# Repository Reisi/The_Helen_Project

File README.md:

# Helen

The Helen Project is a firmware platform for bicycle lights.
It features

- up to 8 modes, each individually configurable
- the modes can be split into groups
- support for remote control connected over BLE
- mode and group configurations with The Helen App
- light-to-light connections with mode synchronization

Currently there are two devices:

- [Helen](HELEN.md), an alternative electronic circuit for the Yinding or KD2 headlight cycling lamps
- [Drake](https://github.com/Reisi/Drake), a multi-purpose PCB, which can be used to build a rear light or a dropper post actuator

## License

This project is licensed under the BSD-2-clause License - see the [license.txt](license.txt) file for details

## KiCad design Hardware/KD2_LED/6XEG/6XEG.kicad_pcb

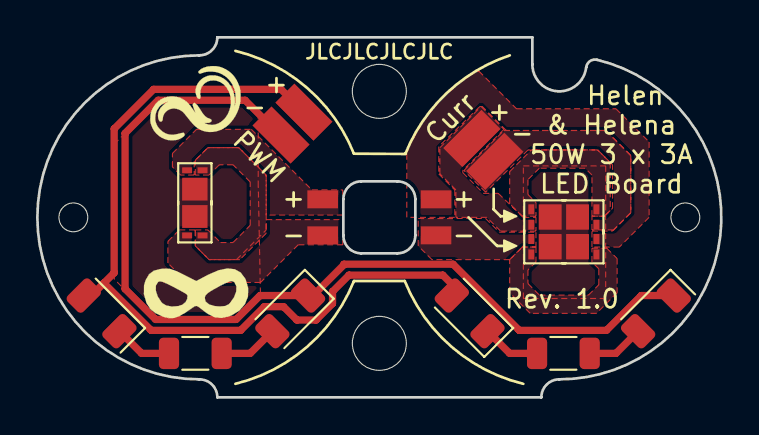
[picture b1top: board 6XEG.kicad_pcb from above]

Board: 2 copper layers, 38.0 x 20.0 mm, 17 parts (0 on the bottom side), 17 nets.

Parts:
D1, D2, D3, D4, D5, D6: LED_PAD; LED_Cree-XE-G
D7, D8, D9, D10: LED; LED_1206_3216Metric
J1: Conn_02x02_Odd_Even; PinHeader_2x02_P2.00mm_Vertical_SMD
J2, J3, J4, J5: Conn_01x01; 1,5x3mm_SMD
R1, R2: R; R_1206_3216Metric

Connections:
unnamed: D1.1, D2.2
unnamed: D1.2, J1.1
unnamed: D1.3, D2.3
unnamed: D2.1, J1.3
unnamed: D3.1, D4.2
unnamed: D3.2, J2.1
unnamed: D3.3, D4.3, D5.3, D6.3
unnamed: D4.1, J3.1
unnamed: D5.1, D6.2
unnamed: D5.2, J1.2
unnamed: D6.1, J1.4
unnamed: D7.1, R1.1
unnamed: D7.2, D8.2, J4.1
unnamed: D8.1, R2.1
unnamed: D9.2, R1.2
unnamed: D9.1, D10.1, J5.1
unnamed: D10.2, R2.2

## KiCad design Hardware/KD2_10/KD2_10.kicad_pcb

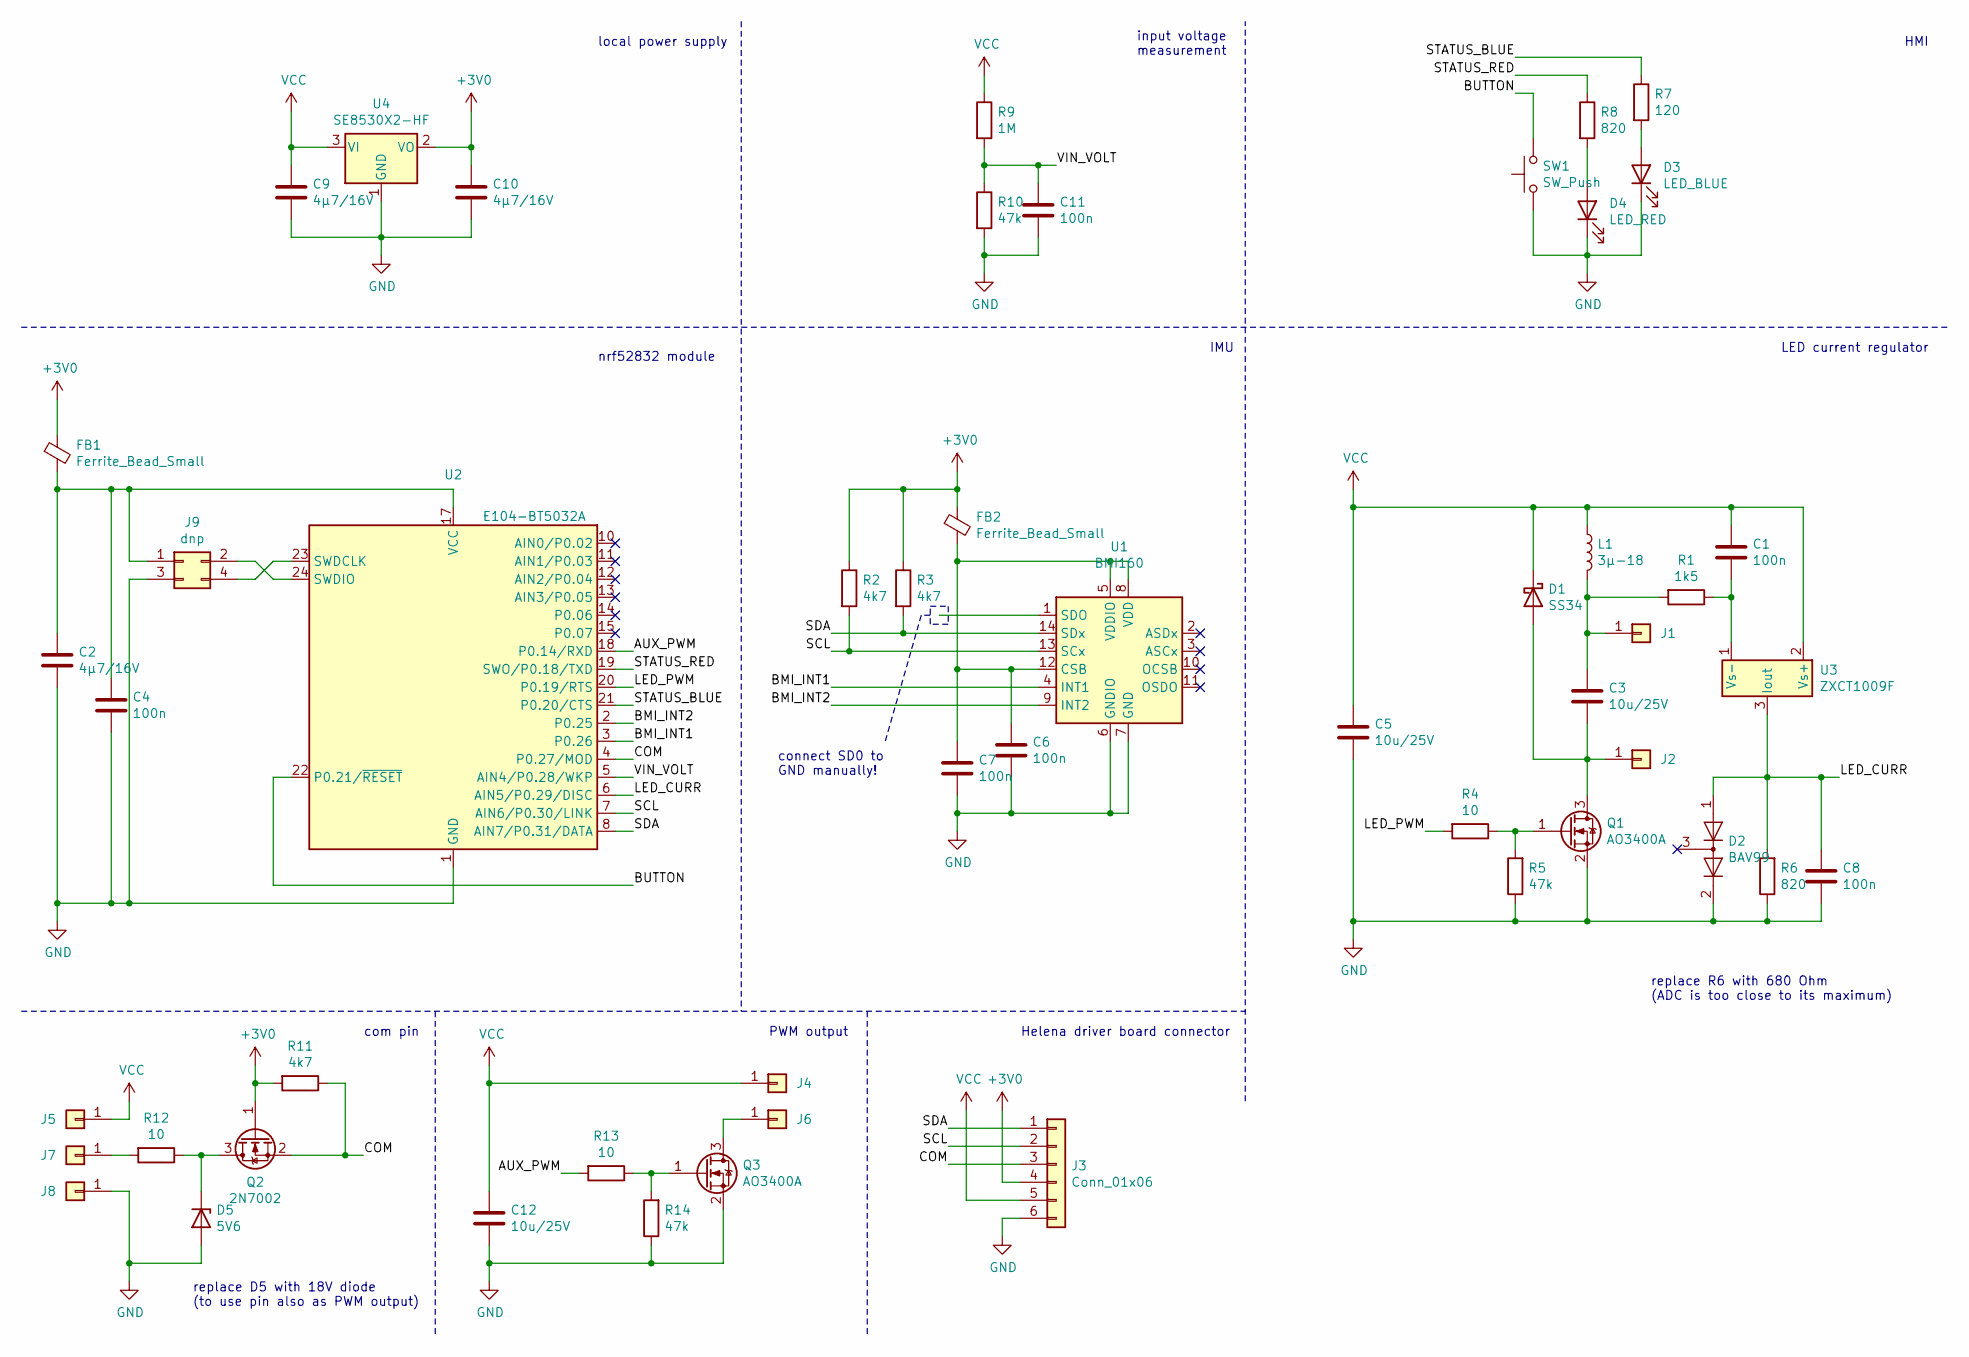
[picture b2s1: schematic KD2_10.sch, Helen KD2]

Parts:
C1, C4, C6, C7, C8, C11: 100n; C_0603_1608Metric; JLC 0603
C2, C9, C10: 4µ7/16V; C_0603_1608Metric; JLC 0603
C3, C5, C12: 10u/25V; C_0805_2012Metric; JLC 0805
D1: SS34; D_SMA; JLC SMA,DO-214AC
D2: BAV99; SOT-23; JLC SOT-23-3
D3: LED_BLUE; LED_0603_1608Metric; JLC LED_0603
D4: LED_RED; LED_0603_1608Metric; JLC LED_0603
D5: 5V6; D_SOT-23_ANK; JLC SOT-23-3
FB1, FB2: Ferrite_Bead_Small; L_0603_1608Metric; JLC 0603
J1, J2, J4, J5, J6, J7, J8: Conn_01x01; 1,5x3mm_SMD
J3: Conn_01x06; PinHeader_1x06_P2.00mm_Vertical
J9: dnp; PinHeader_2x02_P1.27mm_Vertical
L1: 3µ-18; Choke_SMD_Fastron_242418_FPS; JLC IND-SMD
Q1, Q3: AO3400A; SOT-23_AO3400A; JLC SOT-23-3L
Q2: 2N7002; SOT-23; JLC SOT-23-3
R1: 1k5; R_0603_1608Metric; JLC 0603
R2, R3, R11: 4k7; R_0603_1608Metric; JLC 0603
R4, R12, R13: 10; R_0603_1608Metric; JLC 0603
R5, R10, R14: 47k; R_0603_1608Metric; JLC 0603
R6, R8: 820; R_0603_1608Metric; JLC 0603
R7: 120; R_0603_1608Metric; JLC 0603
R9: 1M; R_0603_1608Metric; JLC 0603
SW1: SW_Push; JTP-1138EM; JLC SMD-4_6.0x6.0x4.5P
U1: BMI160; Bosch_LGA-14_3x2.5mm_P0.5mm; JLC LGA-14
U2: E104-BT5032A; JLC WIRELM-SMD
U3: ZXCT1009F; SOT-23; JLC SOT-23-3
U4: SE8530X2-HF; SOT-23_MCP1703; JLC SOT-23-3

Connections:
+3V0: C10.1, FB1.1, FB2.1, J3.4, Q2.1 (G), R2.1, R3.1, R11.2, U4.2 (VO)
/AUX_PWM: R13.2, U2.18 (P0.14/RXD)
/BMI_INT1: U1.4 (INT1), U2.3 (P0.26)
/BMI_INT2: U1.9 (INT2), U2.2 (P0.25)
/BUTTON: SW1.2, U2.22 (P0.21/~RESET)
/COM: J3.3, Q2.2 (S), R11.1, U2.4 (P0.27/MOD)
/LED_CURR: C8.1, D2.1 (K), R6.2, U2.6 (AIN5/P0.29/DISC), U3.3 (Iout)
/LED_PWM: R4.2, U2.20 (P0.19/RTS)
/SCL: J3.2, R2.2, U1.13 (SCx), U2.7 (AIN6/P0.30/LINK)
/SDA: J3.1, R3.2, U1.14 (SDx), U2.8 (AIN7/P0.31/DATA)
/STATUS_BLUE: R7.1, U2.21 (P0.20/CTS)
/STATUS_RED: R8.1, U2.19 (SWO/P0.18/TXD)
/VIN_VOLT: C11.1, R9.2, R10.1, U2.5 (AIN4/P0.28/WKP)
GND: C2.2, C4.2, C5.2, C6.2, C7.2, C8.2, C9.2, C10.2, C11.2, C12.2, D2.2 (A), D3.1 (K), D4.1 (K), D5.2 (A), J3.6, J8.1, J9.3, Q1.2 (S), Q3.2 (S), R5.1, R6.1, R10.2, R14.1, SW1.1, U1.6 (GNDIO), U1.7 (GND), U2.1 (GND), U2.9 (GND), U2.16 (GND), U4.1 (GND)
unnamed: C1.2, R1.1, U3.1 (Vs-)
unnamed: C2.1, C4.1, FB1.2, J9.1, U2.17 (VCC)
unnamed: C3.1, J1.1, L1.2, R1.2
unnamed: C3.2, D1.2 (A), J2.1, Q1.3 (D)
unnamed: C6.1, C7.1, FB2.2, U1.5 (VDDIO), U1.8 (VDD), U1.12 (CSB)
unnamed: D3.2 (A), R7.2
unnamed: D4.2 (A), R8.2
unnamed: D5.1 (K), Q2.3 (D), R12.1
unnamed: J6.1, Q3.3 (D)
unnamed: J7.1, R12.2
unnamed: J9.2, U2.24 (SWDIO)
unnamed: J9.4, U2.23 (SWDCLK)
unnamed: Q1.1 (G), R4.1, R5.2
unnamed: Q3.1 (G), R13.1, R14.2
VCC: C1.1, C5.1, C9.1, C12.1, D1.1 (K), J3.5, J4.1, J5.1, L1.1, R9.1, U3.2 (Vs+), U4.3 (VI)

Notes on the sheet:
com pin
PWM output
Helena driver board connector
nrf52832 module
IMU
local power supply
input voltage measurement
LED current regulator
HMI
connect SD0 to GND manually!
replace D5 with 18V diode (to use pin also as PWM output)
replace R6 with 680 Ohm (ADC is too close to its maximum)

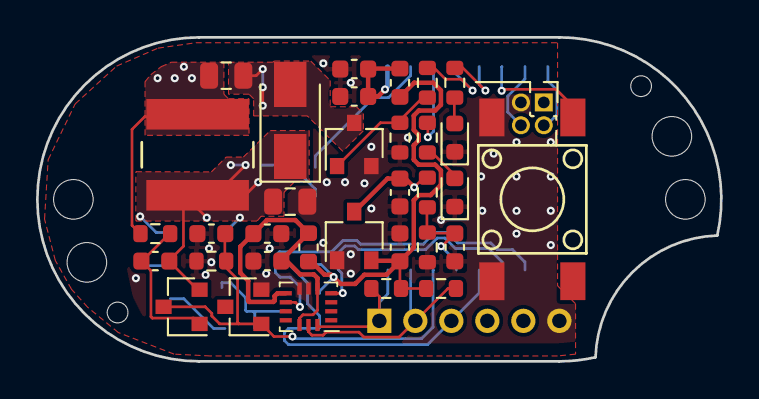
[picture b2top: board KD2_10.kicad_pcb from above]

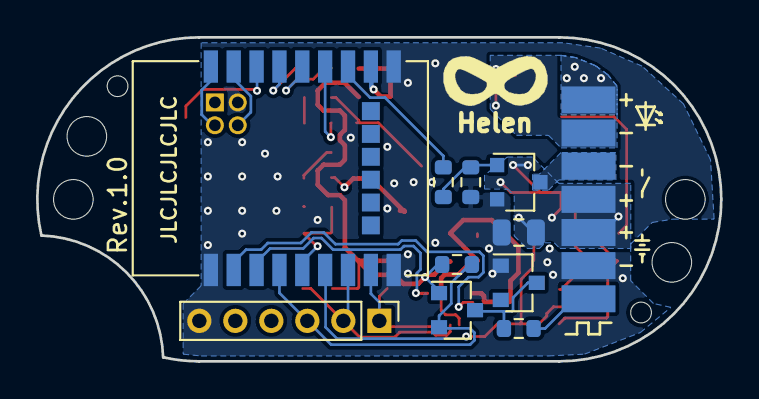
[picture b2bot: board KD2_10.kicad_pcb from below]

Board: 4 copper layers, 38.0 x 18.0 mm, 51 parts (17 on the bottom side), 29 nets.

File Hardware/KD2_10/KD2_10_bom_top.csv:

"Comment","Designator","Footprint","LCSC Part #"
"BMI160","U1","LGA-14","C94021"
"SW_Push","SW1","SMD-4_6.0x6.0x4.5P","C381064"
"SE8530X2-HF","U4","SOT-23-3","C115014"
"4µ7/16V","C9 C10 C2","0603","C19666"
"100n","C4 C7 C11 C1 C8 C6","0603","C14663"
"LED_RED","D4","LED_0603","C2286"
"LED_BLUE","D3","LED_0603","C72041"
"820","R8 R6","0603","C23253"
"120","R7","0603","C22787"
"Ferrite_Bead_Small","FB1 FB2","0603","C1002"
"47k","R10 R5","0603","C25819"
"1M","R9","0603","C22935"
"4k7","R3 R2","0603","C23162"
"10","R4","0603","C22859"
"AO3400A","Q1","SOT-23-3L","C20917"
"3µ-18","L1","IND-SMD","C83456"
"10u/25V","C3 C5","0805","C15850"
"SS34","D1","SMA,DO-214AC","C8678"
"1k5","R1","0603","C22843"
"ZXCT1009F","U3","SOT-23-3","C83670"
"BAV99","D2","SOT-23-3","C2500"
"dnp","J9","",""

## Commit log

2022-11-27 documentation update, adaptation to hardware changes
2024-02-24 added Helen Project Service
2024-03-12 added override mode
2024-06-20 minor bugfixes
2025-06-22 added drake
2025-06-22 documentation fixes
